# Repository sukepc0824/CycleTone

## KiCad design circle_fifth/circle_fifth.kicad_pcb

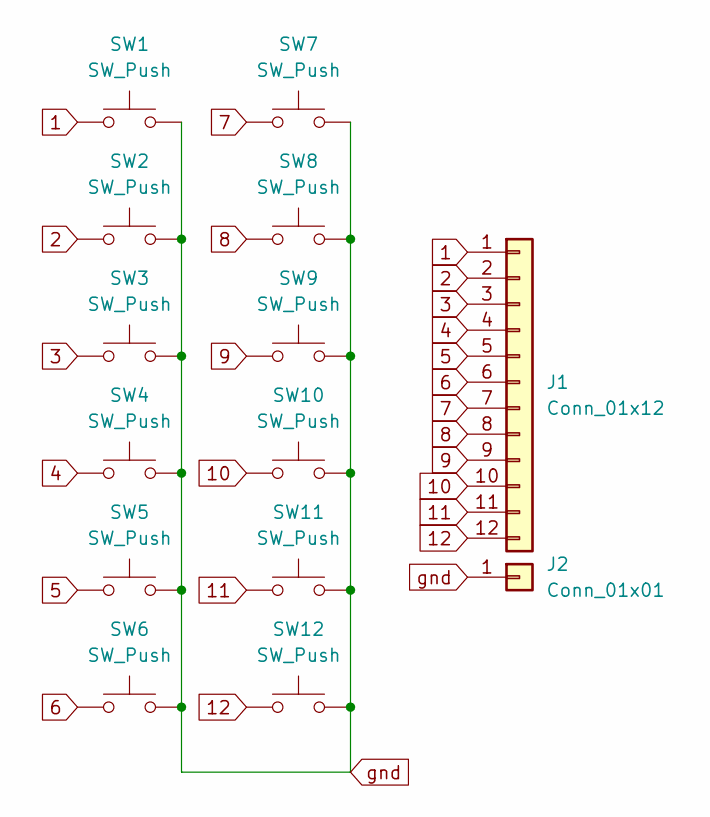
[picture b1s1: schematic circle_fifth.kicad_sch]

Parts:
J1: Conn_01x12; PinHeader_1x12_P2.54mm_Vertical
J2: Conn_01x01; PinHeader_1x01_P2.54mm_Vertical
SW1, SW2, SW3, SW4, SW5, SW6, SW7, SW8, SW9, SW10, SW11, SW12: SW_Push; Kailh_Choc_V1

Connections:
1: J1.1, SW1.1
2: J1.2, SW2.1
3: J1.3, SW3.1
4: J1.4, SW4.1
5: J1.5, SW5.1
6: J1.6, SW6.1
7: J1.7, SW7.1
8: J1.8, SW8.1
9: J1.9, SW9.1
10: J1.10, SW10.1
11: J1.11, SW11.1
12: J1.12, SW12.1
gnd: J2.1, SW1.2, SW2.2, SW3.2, SW4.2, SW5.2, SW6.2, SW7.2, SW8.2, SW9.2, SW10.2, SW11.2, SW12.2

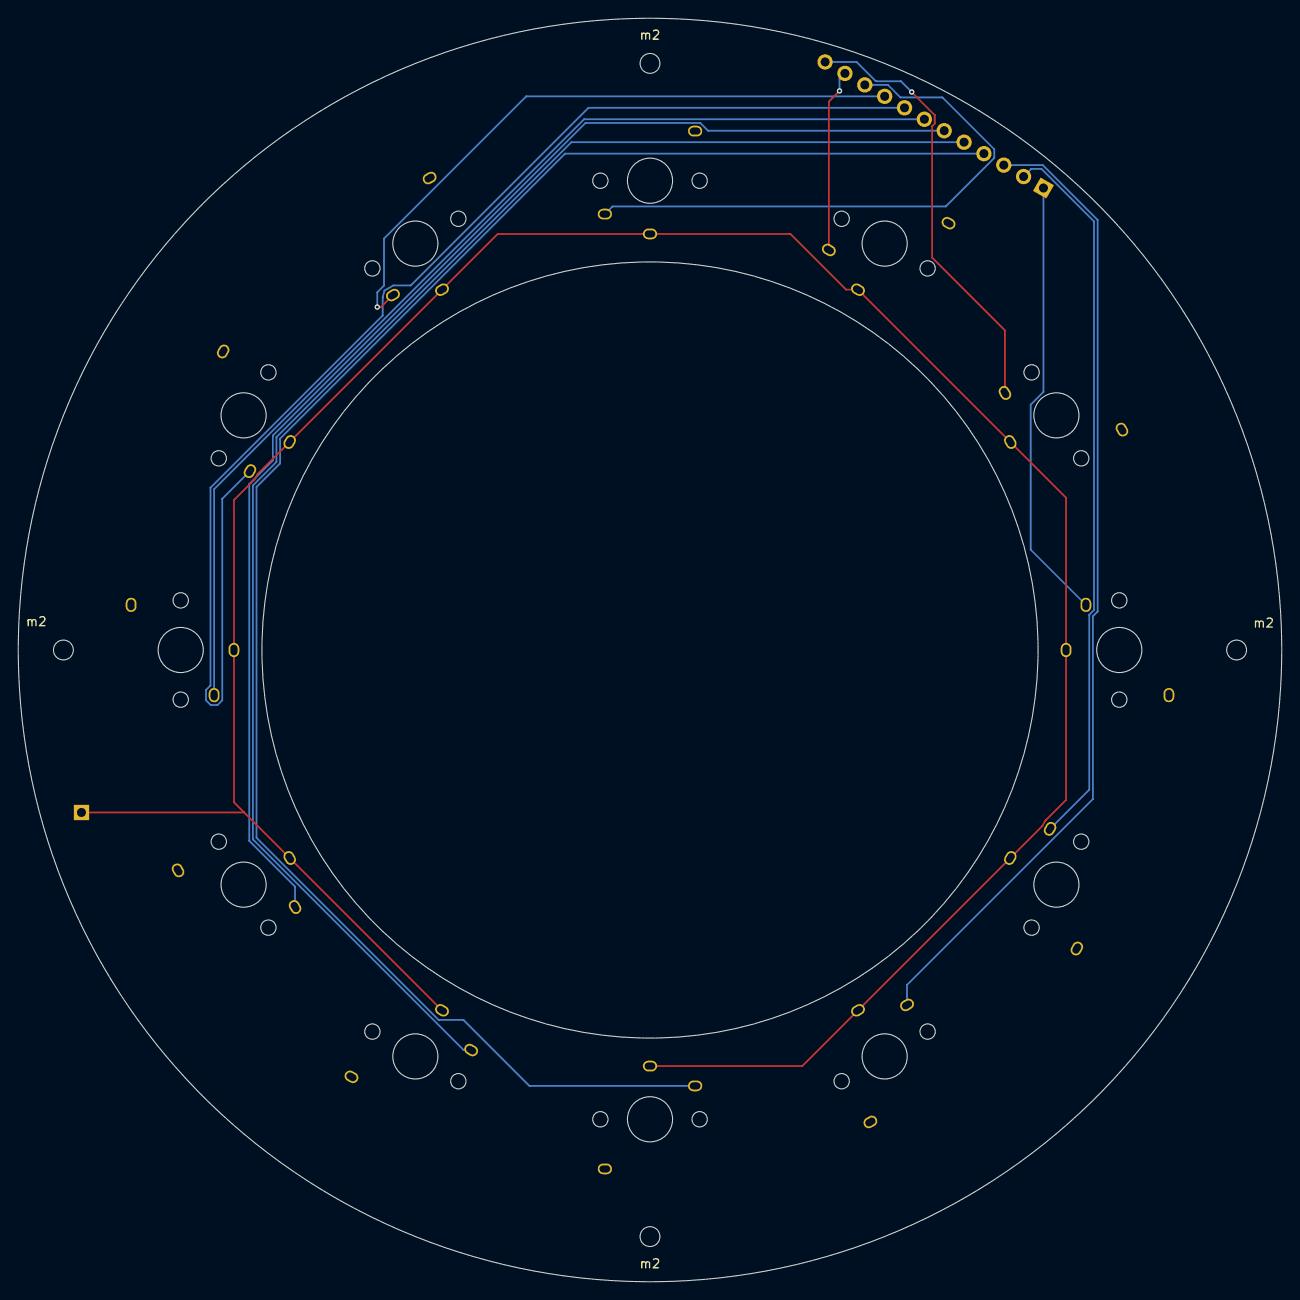
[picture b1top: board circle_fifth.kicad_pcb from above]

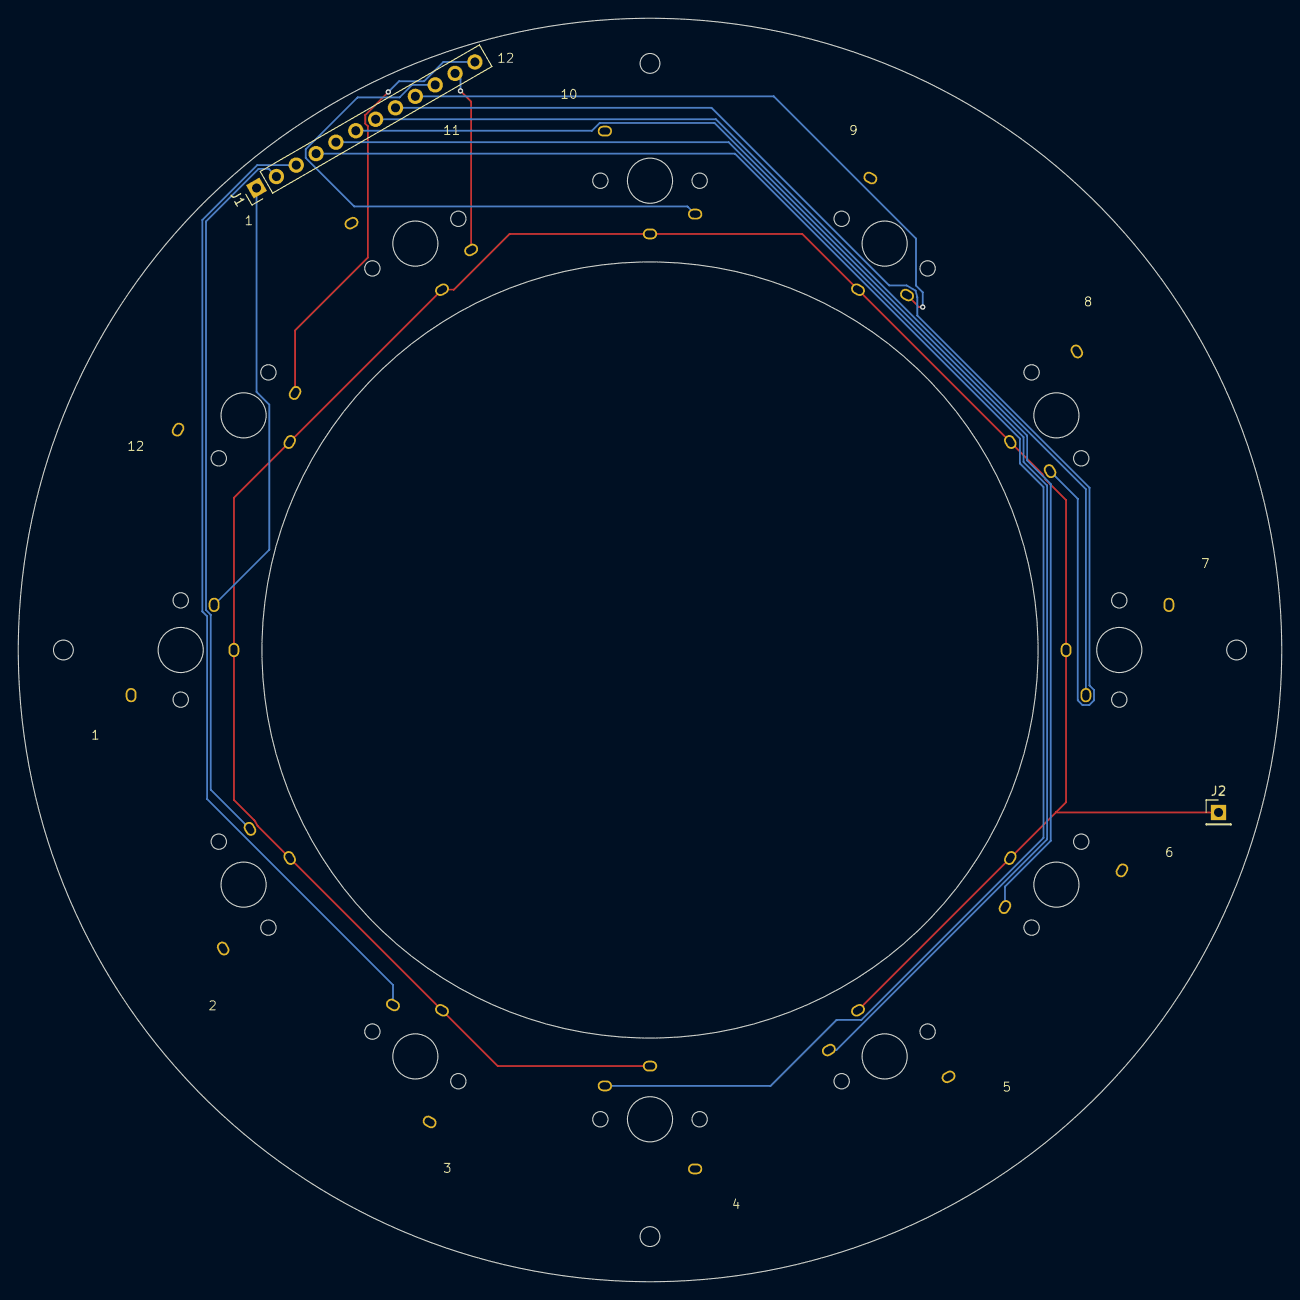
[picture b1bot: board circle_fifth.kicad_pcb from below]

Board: 2 copper layers, 140.0 x 140.0 mm, 18 parts (2 on the bottom side), 13 nets.

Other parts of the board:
m2, m2#2, m2#3, m2#4: MountingHole_2.2mm_M2

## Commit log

2025-06-09 多少見やすく
2025-06-09 音を鳴らせるように
2025-06-09 ミスった２
2025-06-09 だめなのね
2025-06-09 もういいや
2025-06-29 いったん
2025-07-11 コードの変更: 和音解析機能を追加し、次の和音を取得するロジックを改善
2025-07-12 波線矢印の描画機能を追加し、和音の属性に基づいて矢印を描画するロジックを改善
2025-07-12 test
2025-07-12 test2
2025-07-13 テストを追加
2025-07-13 UIの改善
2025-07-15 フォントを変更
2025-08-05 キー入力処理を修正し、'a'と'b'キーに特定の値を割り当てました。また、test3.htmlを新規作成し、UIを改善しました。
2025-08-05 キー入力処理でのイベントキーのログ出力を追加
2025-08-05 非表示か
2025-08-05 ラズパイように位置を調整
2025-08-06 rotate
2025-08-06 rotate2
2025-08-26 一旦実装
2025-08-26 dekita2
2025-09-16 一旦コミット
2025-09-18 ittan
2025-09-20 一旦test
2025-09-20 スクロールを変更
2025-09-21 一旦完成
2025-09-21 完了(がんばった)
2025-09-23 リス名＝評価用
2025-09-24 再生時間の変更
2025-09-24 あぶない
2025-09-25 syusei
2025-09-25 ディレクトリ構造を変更
2025-10-12 ディレクトリ構造を整理
2025-10-19 表示位置を若干更新
2025-10-19 さらに微調整
2025-10-19 さらにさらに美調節
2025-10-19 若干の調整
2025-11-05 習性終わり
2025-11-06 右クリックで更新
2025-11-06 ローカルへ
2026-05-14 一旦commit tonight
